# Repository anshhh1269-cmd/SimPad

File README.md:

hi! 

Welcome to the repo for SimPad, my custom flight simulator controller. I got tired of using my keyboard for everything, so I decided to design and build my own hardware to make flying a lot more immersive.

# Why SimPad?

As an aspiring mechanical engineer with a focus on automotive (cars) and aerospace (planes and rockets), with a slight more interest in the latter, I wanted to build something that would include the mechanics of controlling a plane or a car. GeoFS has always captivated me, but I often found it irritating to use a keyboard and mouse, constantly reaching for the buttons; this frustration led me to the idea of creating a solution that allows us to feel the cockpit at home :)

# How it Works

The Hardware Brain: It uses an STM32 microcontroller, a USB-C port to gain voltage from the computer, a voltage booster, 7 tactical switches, 3 rotary encoders, 1 rotary switch, and one metal toggle. So basically the STM32 uses the USB-C's VBUS-A pad to receive the input voltage of 5V, which is then used to power all of the switches connected to random empty pads on the microcontroller; moreover, the buck converter takes the higher input voltage (5V) and efficiently steps it down to the stable 3.3V required to power your microcontroller and other components. The STM32 is constantly monitoring the status of your various inputs—switches (S1, S2, S3), push buttons (SW9–SW13), and encoders (SW1, SW2, SW3); When you flip a switch, the STM32 detects a voltage change on one of its pins where it runs the firmware to determine what this switch actually does in the context of a flight sim. 

Comms:  The STM32 communicates with your PC via the USB-C connector, through the D+/D- differential data lines; it tells the flight simulator, "Hey, this switch has been flipped!"

Filtering: Capacitors ($C1, C2$) are placed to smooth out voltage noise for stable USB communication.

# PCB and Schemantics

# 3D View of PCB

# 3D enclosure of the PCB

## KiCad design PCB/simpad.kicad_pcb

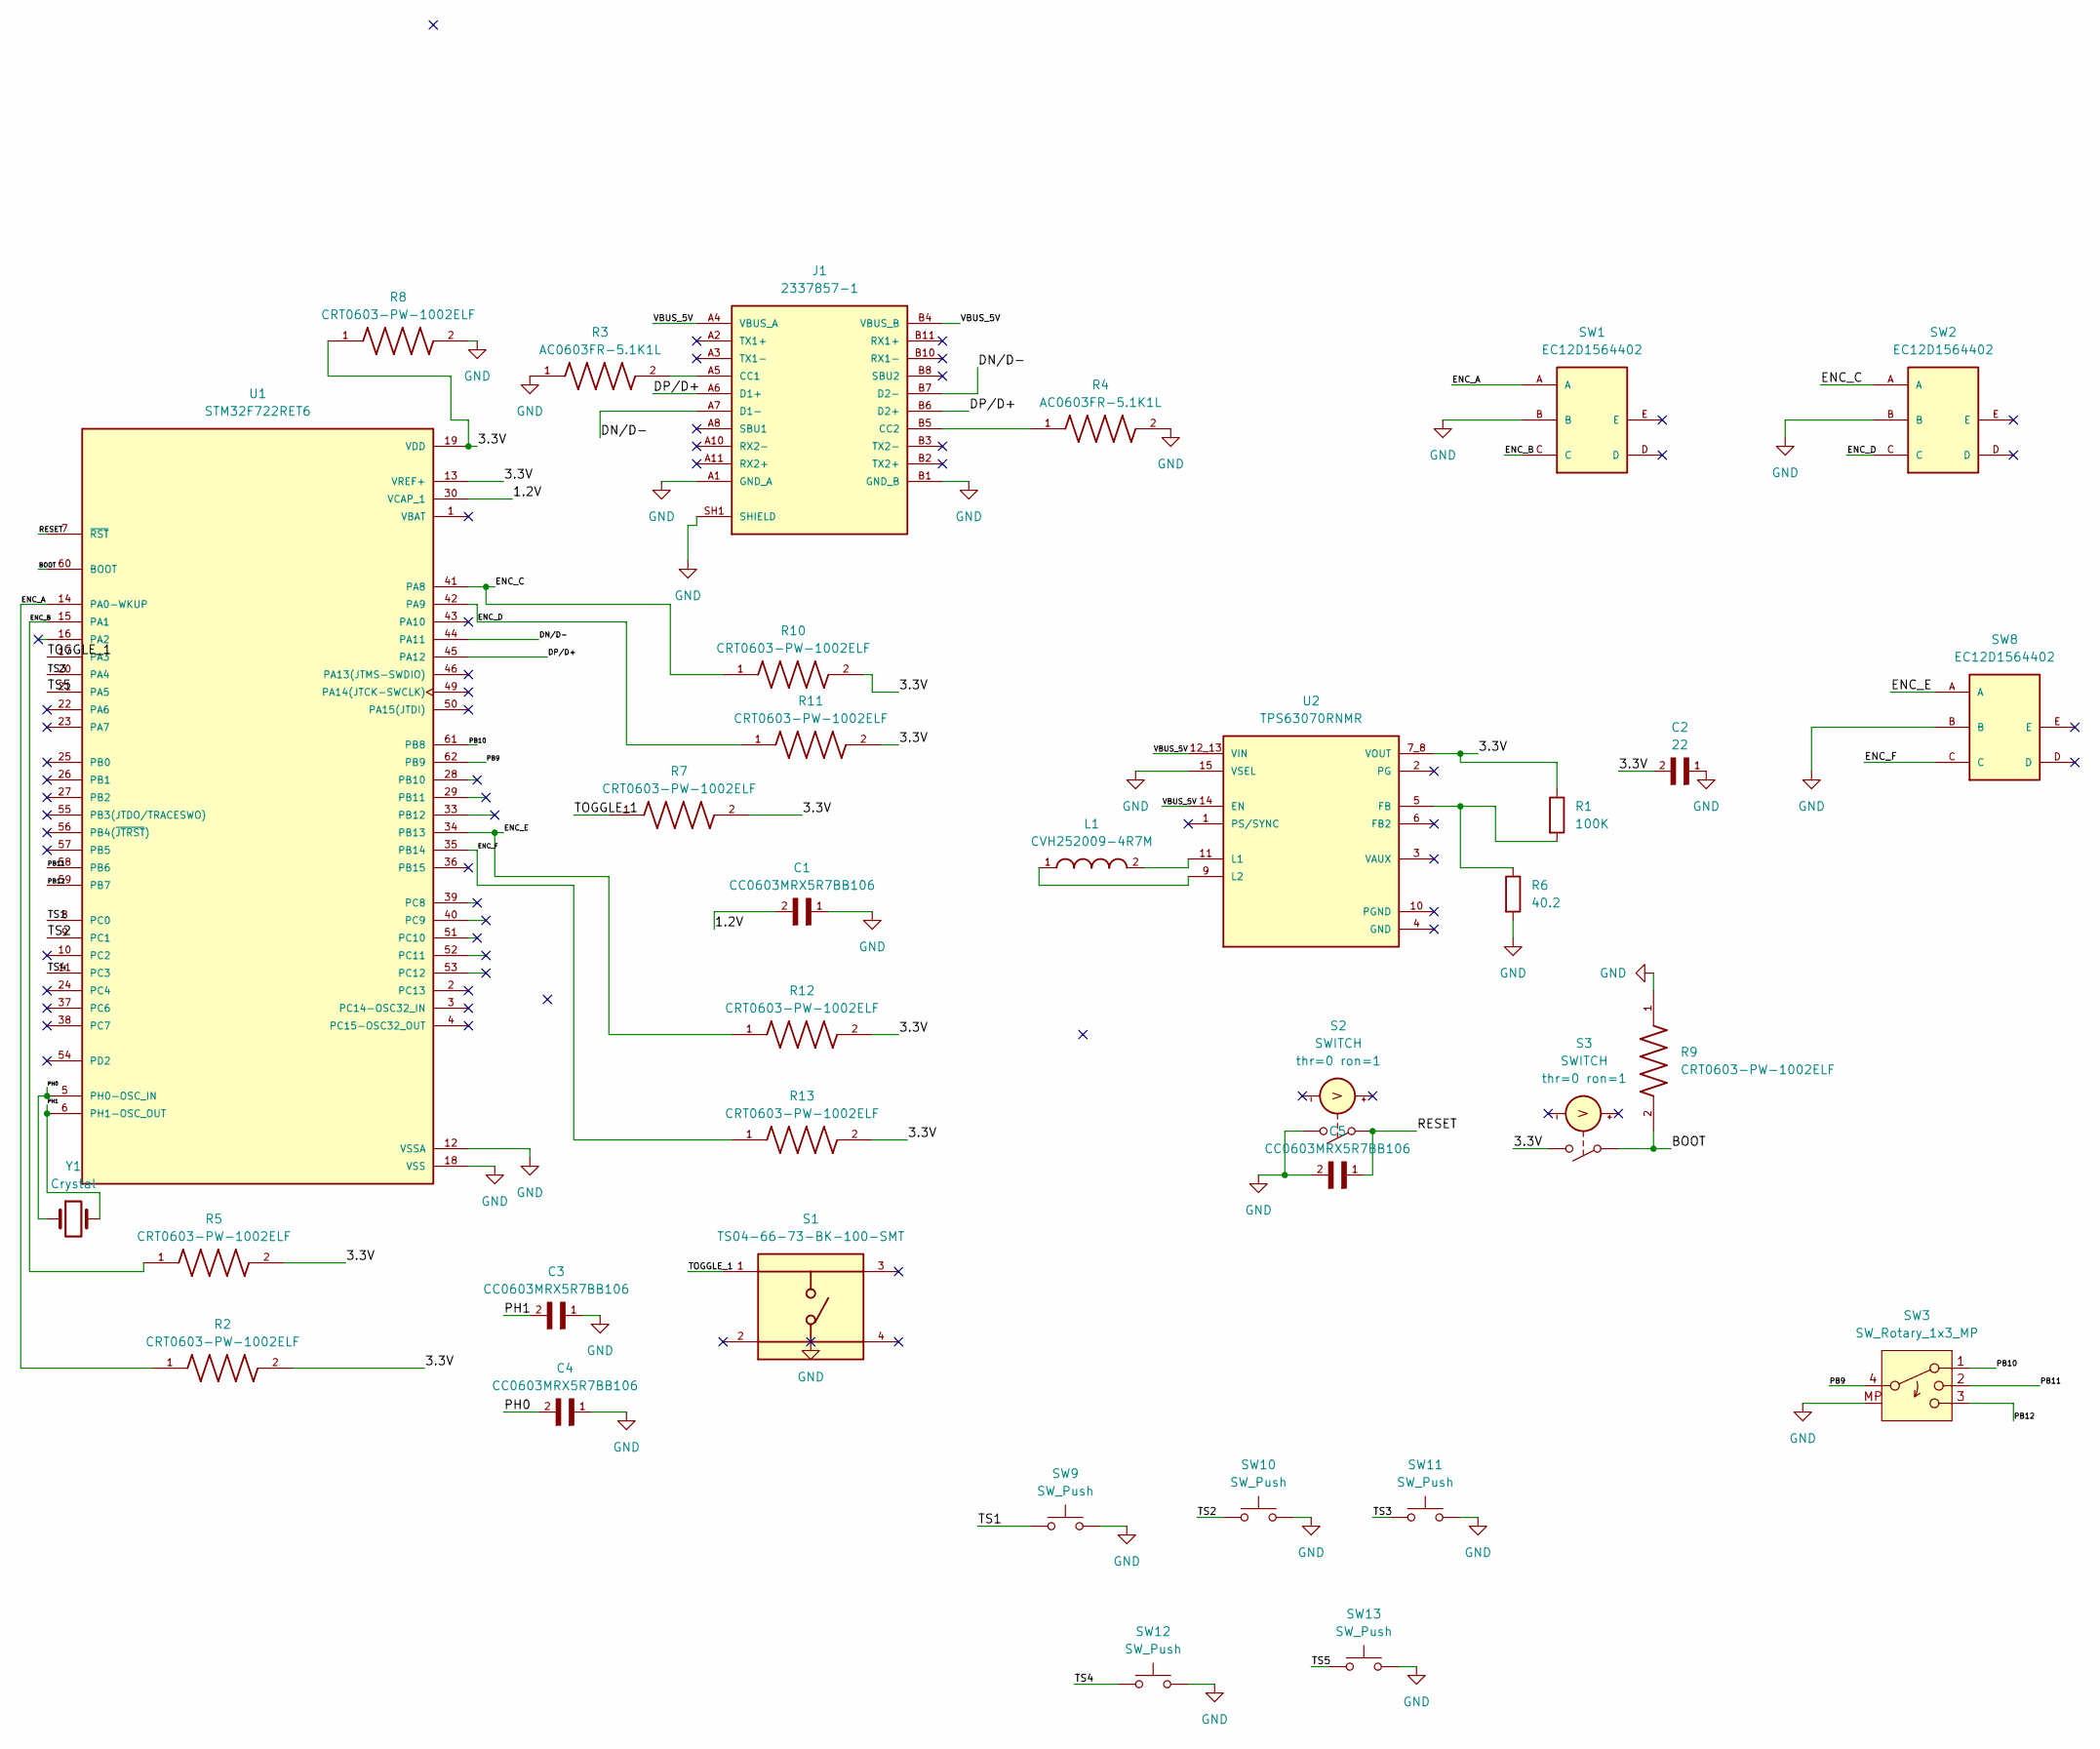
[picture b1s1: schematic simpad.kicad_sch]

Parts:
C1, C3, C4, C5: CC0603MRX5R7BB106; C_0201_0603Metric; DigiKey_Part_Number 311-1822-1-ND
C2: 22; C_0201_0603Metric; DigiKey_Part_Number 311-1822-1-ND
J1: 2337857-1; TE_2337857-1; PARTREV A
L1: CVH252009-4R7M; INDC2520X100N
R1: 100K; R_0603_1608Metric
R2, R5, R7, R8, R9, R10, R11, R12, R13: CRT0603-PW-1002ELF; R_0603_1608Metric
R3, R4: AC0603FR-5.1K1L; R_0603_1608Metric
R6: 40.2; R_0603_1608Metric
S1: TS04-66-73-BK-100-SMT; SW_TS04-66-73-BK-100-SMT; PARTREV 1.0
S2, S3: SWITCH; SW_Push_1TS009xxxx-xxxx-xxxx_6x6x5mm
SW1, SW2, SW8: EC12D1564402; EC12D; FARNELL 2065075
SW3: SW_Rotary_1x3_MP; PinHeader_1x05_P2.54mm_Vertical_SMD_Pin1Left
SW9, SW10, SW11, SW12, SW13: SW_Push; SW_Push_1TS009xxxx-xxxx-xxxx_6x6x5mm
U1: STM32F722RET6; QFP50P1200X1200X160-64N; PARTREV 4
U2: TPS63070RNMR; VREG_TPS63070RNMR; PARTREV B
Y1: Crystal; Crystal_SMD_3215-2Pin_3.2x1.5mm

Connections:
/1.2V: C1.2, U1.30 (VCAP_1)
/BOOT: R9.2, S3.1 (N+), U1.60 (BOOT)
/DN/D-: J1.A7 (D1-), J1.B7 (D2-), U1.44 (PA11)
/DP/D+: J1.A6 (D1+), J1.B6 (D2+), U1.45 (PA12)
/ENC_A: R2.1, SW1.A, U1.14 (PA0-WKUP)
/ENC_B: R5.1, SW1.C, U1.15 (PA1)
/ENC_C: R10.1, SW2.A, U1.41 (PA8)
/ENC_D: R11.1, SW2.C, U1.42 (PA9)
/ENC_E: R12.1, SW8.A, U1.34 (PB13)
/ENC_F: R13.1, SW8.C, U1.35 (PB14)
/PB9: SW3.4, U1.62 (PB9)
/PB10: SW3.1, U1.61 (PB8)
/PB11: SW3.2, U1.58 (PB6)
/PB12: SW3.3, U1.59 (PB7)
/PH0: C4.2, U1.5 (PH0-OSC_IN), Y1.1
/PH1: C3.2, U1.6 (PH1-OSC_OUT), Y1.2
/RESET: C5.1, S2.1 (N+), U1.7 (~RST)
/TOGGLE_1: R7.1, S1.1, U1.17 (PA3)
/TS1: SW9.1, U1.8 (PC0)
/TS2: SW10.1, U1.9 (PC1)
/TS3: SW11.1, U1.20 (PA4)
/TS4: SW12.1, U1.11 (PC3)
/TS5: SW13.1, U1.21 (PA5)
GND: C1.1, C2.1, C3.1, C4.1, C5.2, J1.A1 (GND_A), J1.A12 (GND_A), J1.B1 (GND_B), J1.B12 (GND_B), J1.SH1 (SHIELD), J1.SH2 (SHIELD), J1.SH3 (SHIELD), J1.SH4 (SHIELD), J1.SH5 (SHIELD), J1.SH6 (SHIELD), R3.1, R4.2, R6.2, R8.2, R9.1, S2.2 (N-), SW1.B, SW2.B, SW3.MP, SW8.B, SW9.2, SW10.2, SW11.2, SW12.2, SW13.2, U1.12 (VSSA), U1.18 (VSS), U1.31 (VSS), U1.47 (VSS), U1.63 (VSS), U2.15 (VSEL)
unnamed: J1.A5 (CC1), R3.2
unnamed: J1.B5 (CC2), R4.1
unnamed: R1.2, R6.1, U2.5 (FB)
unnamed: L1.2, U2.11 (L1)
unnamed: L1.1, U2.9 (L2)
VBUS_A: J1.A4 (VBUS_A), J1.A9 (VBUS_A), J1.B4 (VBUS_B), J1.B9 (VBUS_B), U2.12_13 (VIN), U2.14 (EN)
VDD: C2.2, R1.1, R2.2, R5.2, R7.2, R8.1, R10.2, R11.2, R12.2, R13.2, S3.2 (N-), U1.13 (VREF+), U1.19 (VDD), U1.32 (VDD), U1.48 (VDD), U1.64 (VDD), U2.7_8 (VOUT)

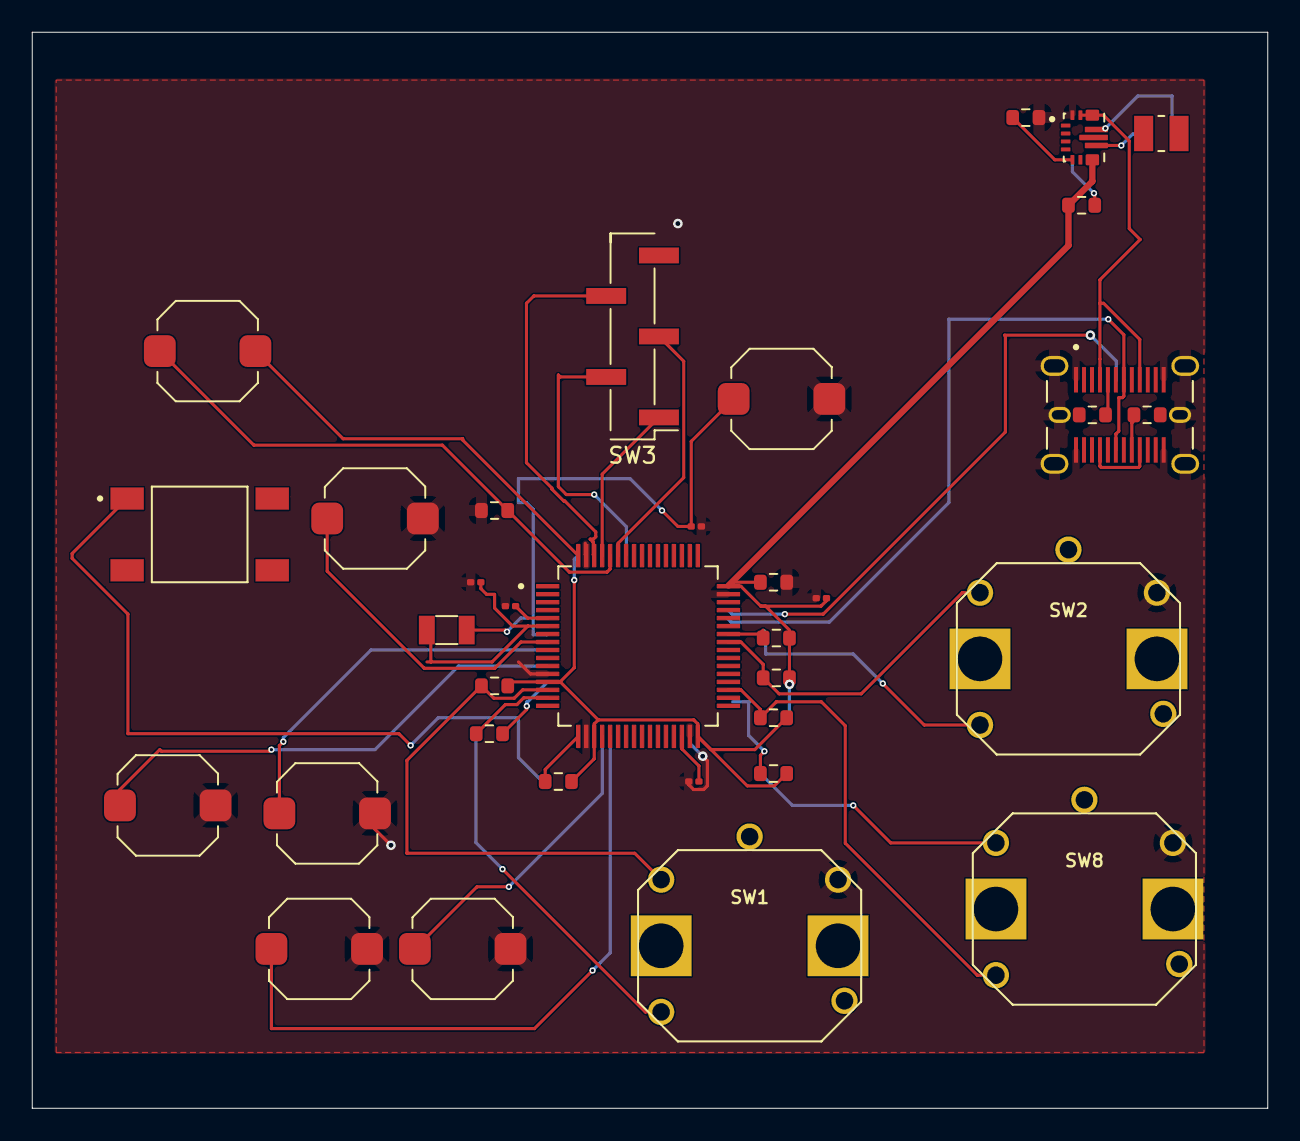
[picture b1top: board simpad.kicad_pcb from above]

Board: 2 copper layers, 77.5 x 67.5 mm, 35 parts (0 on the bottom side), 31 nets.

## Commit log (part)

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2026-06-30 Rename simpad.kicad_sch to Schematic/simpad.kicad_sch
2026-06-30 Rename simpad.pdf to Schematic/simpad.pdf
2026-06-30 Rename simpad-B_Cu.gbr to Gerber/simpad-B_Cu.gbr
2026-06-30 Rename simpad-Edge_Cuts.gbr to Gerber/simpad-Edge_Cuts.gbr
2026-06-30 Rename simpad-F_Cu.gbr to Gerber/simpad-F_Cu.gbr
2026-06-30 Rename simpad-F_Mask.gbr to Gerber/simpad-F_Mask.gbr
2026-06-30 Rename simpad-F_Paste.gbr to Gerber/simpad-F_Paste.gbr
2026-06-30 Rename simpad-F_Silkscreen.gbr to Gerber/simpad-F_Silkscreen.gbr
2026-06-30 Rename simpad-NPTH.drl to Gerber/simpad-NPTH.drl
2026-06-30 Rename simpad-PTH.drl to Gerber/simpad-PTH.drl
2026-06-30 Rename simpad-job.gbrjob to Gerber/simpad-job.gbrjob
